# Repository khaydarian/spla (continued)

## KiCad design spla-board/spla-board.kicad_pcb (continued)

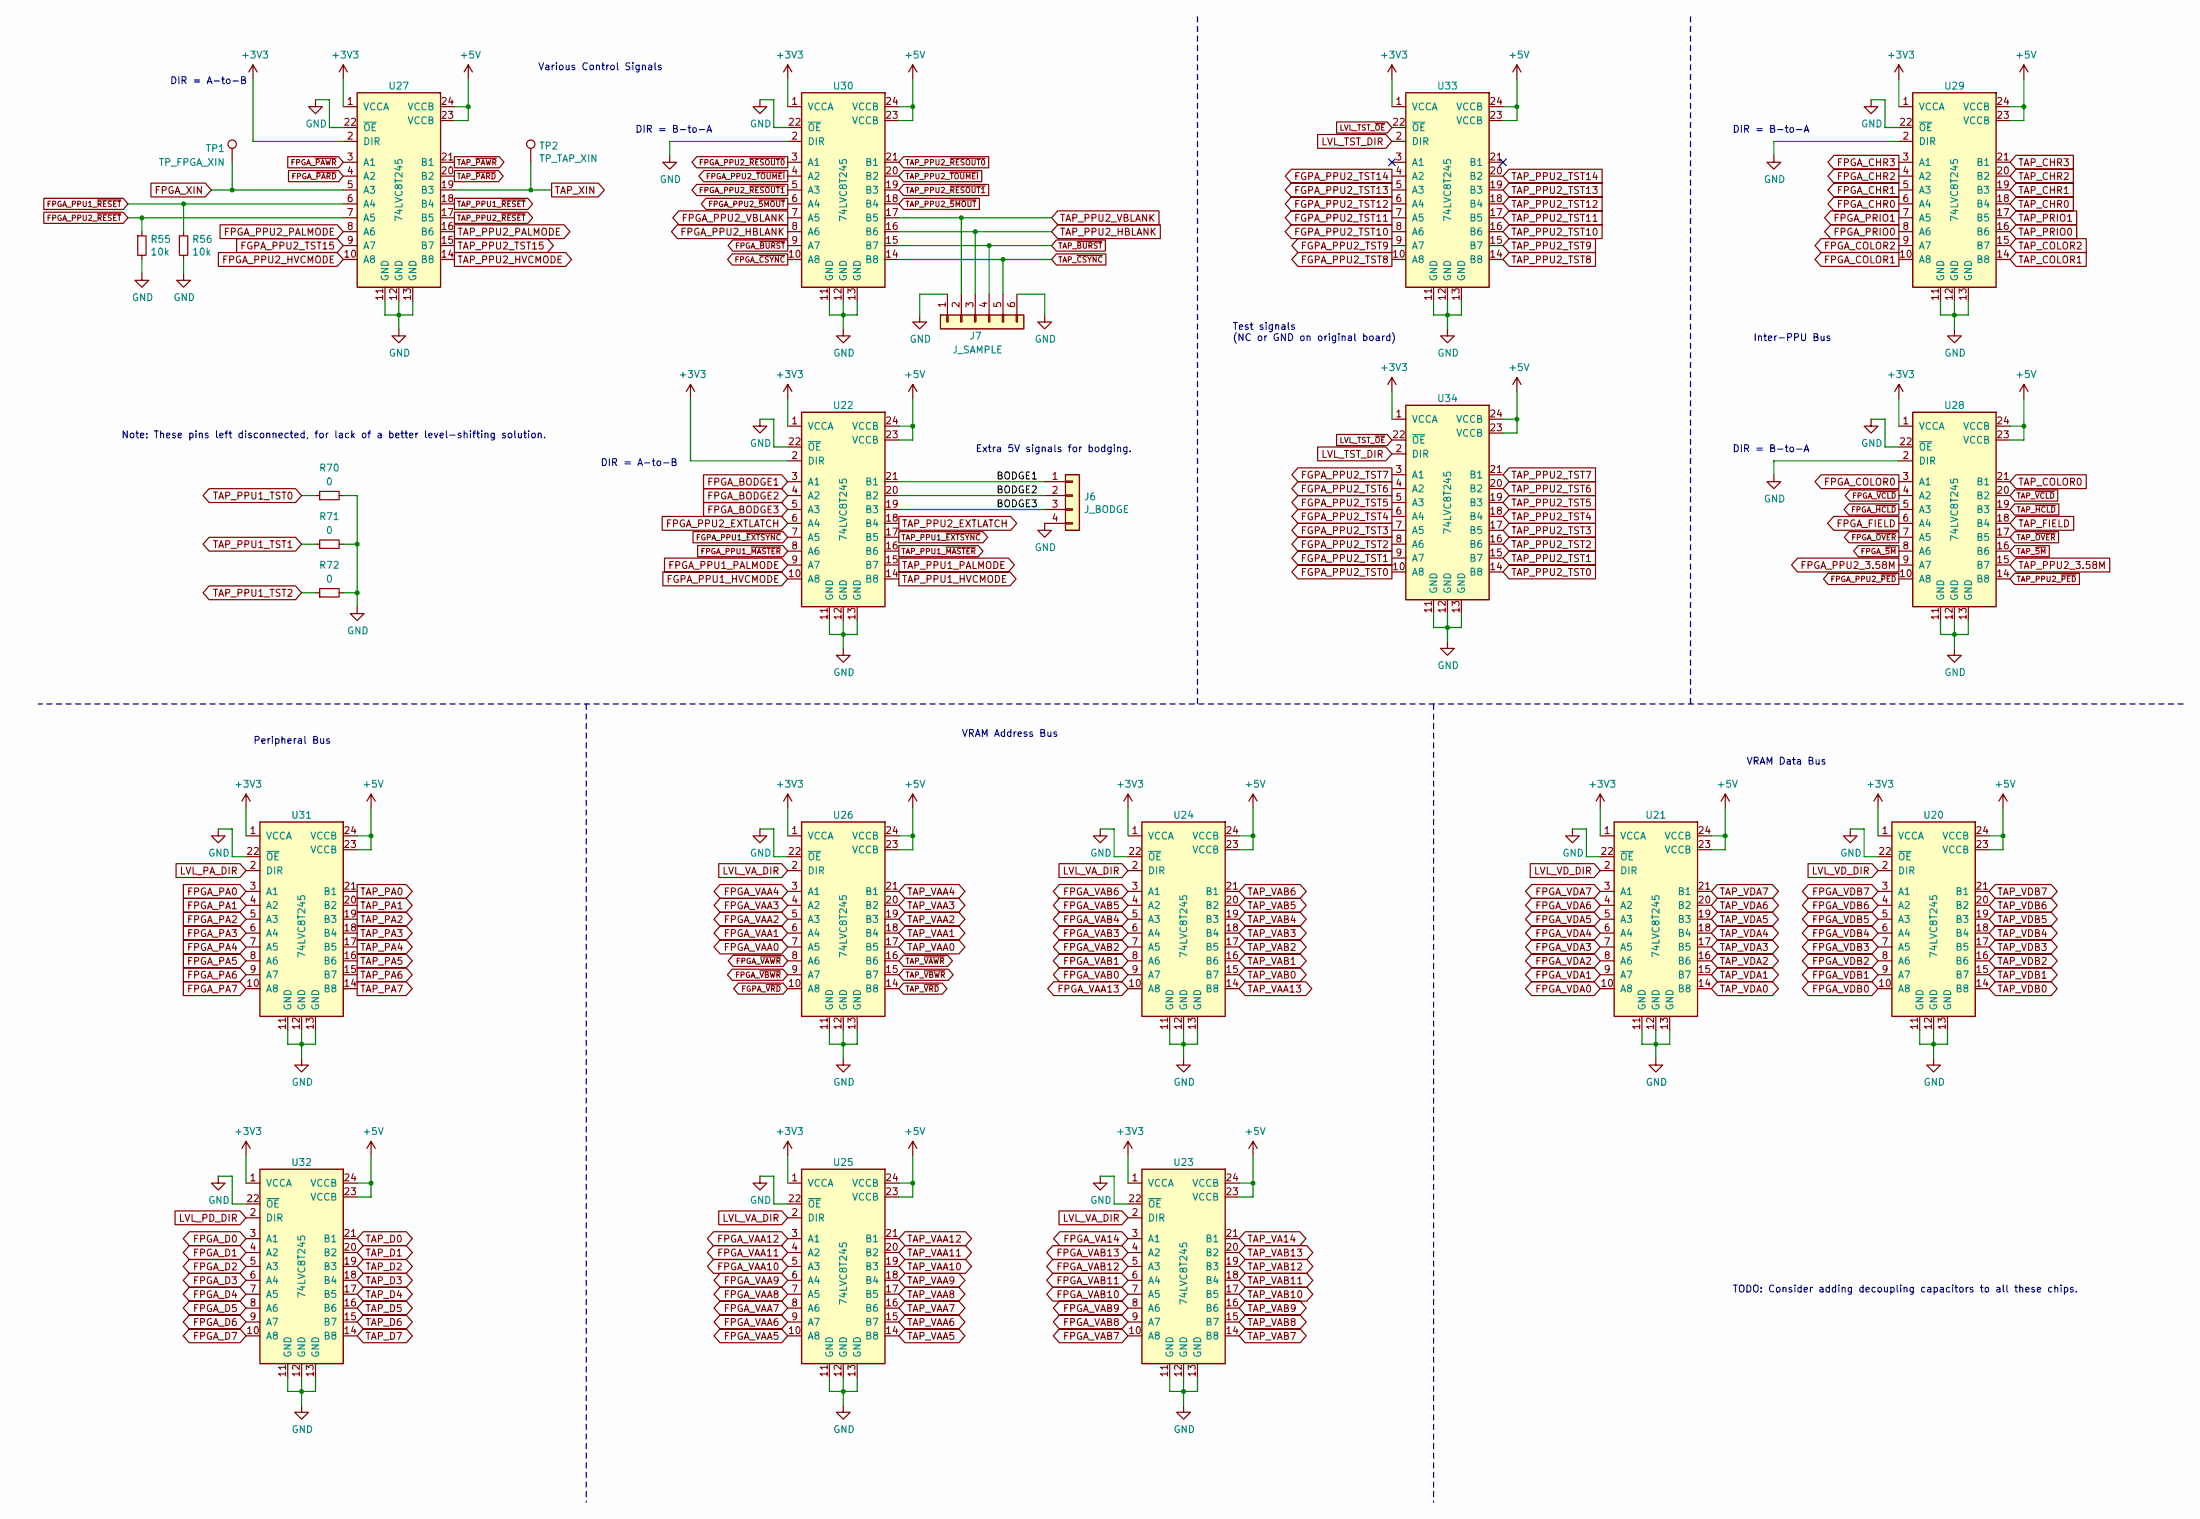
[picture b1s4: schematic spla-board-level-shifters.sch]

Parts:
J6: J_BODGE; PinHeader_1x04_P2.54mm_Vertical; Digikey S1011EC-40-ND
J7: J_SAMPLE; PinHeader_1x06_P2.54mm_Vertical; Digikey S1011EC-40-ND
R55, R56: 10k; R_0603_1608Metric; Digikey RMCF0603JT10K0CT-ND
R70, R71, R72: 0; R_0603_1608Metric; Digikey 2019-RK73Z1JTTDCT-ND
TP1: TP_FPGA_XIN; TestPoint_Pad_D1.0mm; Digikey N/A
TP2: TP_TAP_XIN; TestPoint_Pad_D1.0mm; Digikey N/A
U20, U21, U22, U23, U24, U25, U26, U27, U28, U29, U30, U31, U32, U33, U34: 74LVC8T245; TSSOP-24_4.4x7.8mm_P0.65mm; Digikey 296-18593-1-ND

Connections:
+5V: U20.23 (VCCB), U20.24 (VCCB), U21.23 (VCCB), U21.24 (VCCB), U22.23 (VCCB), U22.24 (VCCB), U23.23 (VCCB), U23.24 (VCCB), U24.23 (VCCB), U24.24 (VCCB), U25.23 (VCCB), U25.24 (VCCB), U26.23 (VCCB), U26.24 (VCCB), U27.23 (VCCB), U27.24 (VCCB), U28.23 (VCCB), U28.24 (VCCB), U29.23 (VCCB), U29.24 (VCCB), U30.23 (VCCB), U30.24 (VCCB), U31.23 (VCCB), U31.24 (VCCB), U32.23 (VCCB), U32.24 (VCCB), U33.23 (VCCB), U33.24 (VCCB), U34.23 (VCCB), U34.24 (VCCB); also elsewhere on the board
/SPLA Board - Level Shifters/BODGE1: J6.1, U22.21 (B1)
/SPLA Board - Level Shifters/BODGE2: J6.2, U22.20 (B2)
/SPLA Board - Level Shifters/BODGE3: J6.3, U22.19 (B3)
FGPA_PPU1_HVCMODE: U22.10 (A8); also elsewhere on the board
FGPA_PPU1_~EXTSYNC~: U22.7 (A5); also elsewhere on the board
FGPA_PPU2_TST0: U34.10 (A8); also elsewhere on the board
FGPA_PPU2_TST1: U34.9 (A7); also elsewhere on the board
FGPA_PPU2_TST2: U34.8 (A6); also elsewhere on the board
FGPA_PPU2_TST3: U34.7 (A5); also elsewhere on the board
FGPA_PPU2_TST4: U34.6 (A4); also elsewhere on the board
FGPA_PPU2_TST5: U34.5 (A3); also elsewhere on the board
FGPA_PPU2_TST6: U34.4 (A2); also elsewhere on the board
FGPA_PPU2_TST7: U34.3 (A1); also elsewhere on the board
FGPA_PPU2_TST8: U33.10 (A8); also elsewhere on the board
FGPA_PPU2_TST9: U33.9 (A7); also elsewhere on the board
FGPA_PPU2_TST10: U33.8 (A6); also elsewhere on the board
FGPA_PPU2_TST11: U33.7 (A5); also elsewhere on the board
FGPA_PPU2_TST12: U33.6 (A4); also elsewhere on the board
FGPA_PPU2_TST13: U33.5 (A3); also elsewhere on the board
FGPA_PPU2_TST14: U33.4 (A2); also elsewhere on the board
FGPA_PPU2_TST15: U27.9 (A7); also elsewhere on the board
FGPA_~VRD~: U26.10 (A8); also elsewhere on the board
FPGA_BODGE1: U22.3 (A1); also elsewhere on the board
FPGA_BODGE2: U22.4 (A2); also elsewhere on the board
FPGA_BODGE3: U22.5 (A3); also elsewhere on the board
FPGA_CHR0: U29.6 (A4); also elsewhere on the board
FPGA_CHR1: U29.5 (A3); also elsewhere on the board
FPGA_CHR2: U29.4 (A2); also elsewhere on the board
FPGA_CHR3: U29.3 (A1); also elsewhere on the board
FPGA_COLOR0: U28.3 (A1); also elsewhere on the board
FPGA_COLOR1: U29.10 (A8); also elsewhere on the board
FPGA_COLOR2: U29.9 (A7); also elsewhere on the board
FPGA_D0: U32.3 (A1); also elsewhere on the board
FPGA_D1: U32.4 (A2); also elsewhere on the board
FPGA_D2: U32.5 (A3); also elsewhere on the board
FPGA_D3: U32.6 (A4); also elsewhere on the board
FPGA_D4: U32.7 (A5); also elsewhere on the board
FPGA_D5: U32.8 (A6); also elsewhere on the board
FPGA_D6: U32.9 (A7); also elsewhere on the board
FPGA_D7: U32.10 (A8); also elsewhere on the board
FPGA_FIELD: U28.6 (A4); also elsewhere on the board
FPGA_PA0: U31.3 (A1); also elsewhere on the board
FPGA_PA1: U31.4 (A2); also elsewhere on the board
FPGA_PA2: U31.5 (A3); also elsewhere on the board
FPGA_PA3: U31.6 (A4); also elsewhere on the board
FPGA_PA4: U31.7 (A5); also elsewhere on the board
FPGA_PA5: U31.8 (A6); also elsewhere on the board
FPGA_PA6: U31.9 (A7); also elsewhere on the board
FPGA_PA7: U31.10 (A8); also elsewhere on the board
FPGA_PPU1_PALMODE: U22.9 (A7); also elsewhere on the board
FPGA_PPU1_~MASTER~: U22.8 (A6); also elsewhere on the board
FPGA_PPU1_~RESET~: R56.1, U27.6 (A4); also elsewhere on the board
FPGA_PPU2_3.58M: U28.9 (A7); also elsewhere on the board
FPGA_PPU2_EXTLATCH: U22.6 (A4); also elsewhere on the board
FPGA_PPU2_HBLANK: U30.8 (A6); also elsewhere on the board
FPGA_PPU2_HVCMODE: U27.10 (A8); also elsewhere on the board
FPGA_PPU2_PALMODE: U27.8 (A6); also elsewhere on the board
FPGA_PPU2_VBLANK: U30.7 (A5); also elsewhere on the board
FPGA_PPU2_~5MOUT~: U30.6 (A4); also elsewhere on the board
FPGA_PPU2_~PED~: U28.10 (A8); also elsewhere on the board
FPGA_PPU2_~RESET~: R55.1, U27.7 (A5); also elsewhere on the board
FPGA_PPU2_~RESOUT0~: U30.3 (A1); also elsewhere on the board
FPGA_PPU2_~RESOUT1~: U30.5 (A3); also elsewhere on the board
FPGA_PPU2_~TOUMEI~: U30.4 (A2); also elsewhere on the board
FPGA_PRIO0: U29.8 (A6); also elsewhere on the board
FPGA_PRIO1: U29.7 (A5); also elsewhere on the board
FPGA_VA14: U23.3 (A1); also elsewhere on the board
FPGA_VAA0: U26.7 (A5); also elsewhere on the board
FPGA_VAA1: U26.6 (A4); also elsewhere on the board
FPGA_VAA2: U26.5 (A3); also elsewhere on the board
FPGA_VAA3: U26.4 (A2); also elsewhere on the board
FPGA_VAA4: U26.3 (A1); also elsewhere on the board
FPGA_VAA5: U25.10 (A8); also elsewhere on the board
FPGA_VAA6: U25.9 (A7); also elsewhere on the board
FPGA_VAA7: U25.8 (A6); also elsewhere on the board
FPGA_VAA8: U25.7 (A5); also elsewhere on the board
FPGA_VAA9: U25.6 (A4); also elsewhere on the board
FPGA_VAA10: U25.5 (A3); also elsewhere on the board
FPGA_VAA11: U25.4 (A2); also elsewhere on the board
FPGA_VAA12: U25.3 (A1); also elsewhere on the board
FPGA_VAA13: U24.10 (A8); also elsewhere on the board
FPGA_VAB0: U24.9 (A7); also elsewhere on the board
FPGA_VAB1: U24.8 (A6); also elsewhere on the board
FPGA_VAB2: U24.7 (A5); also elsewhere on the board
FPGA_VAB3: U24.6 (A4); also elsewhere on the board
FPGA_VAB4: U24.5 (A3); also elsewhere on the board
FPGA_VAB5: U24.4 (A2); also elsewhere on the board
FPGA_VAB6: U24.3 (A1); also elsewhere on the board
FPGA_VAB7: U23.10 (A8); also elsewhere on the board
FPGA_VAB8: U23.9 (A7); also elsewhere on the board
FPGA_VAB9: U23.8 (A6); also elsewhere on the board
FPGA_VAB10: U23.7 (A5); also elsewhere on the board
FPGA_VAB11: U23.6 (A4); also elsewhere on the board
FPGA_VAB12: U23.5 (A3); also elsewhere on the board
FPGA_VAB13: U23.4 (A2); also elsewhere on the board
FPGA_VDA0: U21.10 (A8); also elsewhere on the board
FPGA_VDA1: U21.9 (A7); also elsewhere on the board
FPGA_VDA2: U21.8 (A6); also elsewhere on the board
FPGA_VDA3: U21.7 (A5); also elsewhere on the board
FPGA_VDA4: U21.6 (A4); also elsewhere on the board
FPGA_VDA5: U21.5 (A3); also elsewhere on the board
FPGA_VDA6: U21.4 (A2); also elsewhere on the board
FPGA_VDA7: U21.3 (A1); also elsewhere on the board
FPGA_VDB0: U20.10 (A8); also elsewhere on the board
FPGA_VDB1: U20.9 (A7); also elsewhere on the board
FPGA_VDB2: U20.8 (A6); also elsewhere on the board
FPGA_VDB3: U20.7 (A5); also elsewhere on the board
FPGA_VDB4: U20.6 (A4); also elsewhere on the board
FPGA_VDB5: U20.5 (A3); also elsewhere on the board
FPGA_VDB6: U20.4 (A2); also elsewhere on the board
FPGA_VDB7: U20.3 (A1); also elsewhere on the board
FPGA_XIN: TP1.1, U27.5 (A3); also elsewhere on the board
FPGA_~5M~: U28.8 (A6); also elsewhere on the board
FPGA_~BURST~: U30.9 (A7); also elsewhere on the board
FPGA_~CSYNC~: U30.10 (A8); also elsewhere on the board
FPGA_~HCLD: U28.5 (A3); also elsewhere on the board
FPGA_~OVER~: U28.7 (A5); also elsewhere on the board
FPGA_~PARD~: U27.4 (A2); also elsewhere on the board
FPGA_~PAWR~: U27.3 (A1); also elsewhere on the board
FPGA_~VAWR~: U26.8 (A6); also elsewhere on the board
FPGA_~VBWR~: U26.9 (A7); also elsewhere on the board
FPGA_~VCLD~: U28.4 (A2); also elsewhere on the board
GND: J6.4, J7.1, J7.6, R55.2, R56.2, R70.2, R71.2, R72.2, U20.11 (GND), U20.12 (GND), U20.13 (GND), U20.22 (~OE), U21.11 (GND), U21.12 (GND), U21.13 (GND), U21.22 (~OE), U22.11 (GND), U22.12 (GND), U22.13 (GND), U22.22 (~OE), U23.11 (GND), U23.12 (GND), U23.13 (GND), U23.22 (~OE), U24.11 (GND), U24.12 (GND), U24.13 (GND), U24.22 (~OE), U25.11 (GND), U25.12 (GND), U25.13 (GND), U25.22 (~OE), U26.11 (GND), U26.12 (GND), U26.13 (GND), U26.22 (~OE), U27.11 (GND), U27.12 (GND), U27.13 (GND), U27.22 (~OE), U28.2 (DIR), U28.11 (GND), U28.12 (GND), U28.13 (GND), U28.22 (~OE), U29.2 (DIR), U29.11 (GND), U29.12 (GND), U29.13 (GND), U29.22 (~OE), U30.2 (DIR), U30.11 (GND), U30.12 (GND), U30.13 (GND), U30.22 (~OE), U31.11 (GND), U31.12 (GND), U31.13 (GND), U31.22 (~OE), U32.11 (GND), U32.12 (GND), U32.13 (GND), U32.22 (~OE), U33.11 (GND), U33.12 (GND), U33.13 (GND), U34.11 (GND), U34.12 (GND), U34.13 (GND); also elsewhere on the board
LVL_PA_DIR: U31.2 (DIR); also elsewhere on the board
LVL_PD_DIR: U32.2 (DIR); also elsewhere on the board
LVL_TST_DIR: U33.2 (DIR), U34.2 (DIR); also elsewhere on the board
LVL_TST_~OE~: U33.22 (~OE), U34.22 (~OE); also elsewhere on the board
LVL_VA_DIR: U23.2 (DIR), U24.2 (DIR), U25.2 (DIR), U26.2 (DIR); also elsewhere on the board
LVL_VD_DIR: U20.2 (DIR), U21.2 (DIR); also elsewhere on the board
TAP_CHR0: U29.18 (B4); also elsewhere on the board
TAP_CHR1: U29.19 (B3); also elsewhere on the board
TAP_CHR2: U29.20 (B2); also elsewhere on the board
TAP_CHR3: U29.21 (B1); also elsewhere on the board
TAP_COLOR0: U28.21 (B1); also elsewhere on the board
TAP_COLOR1: U29.14 (B8); also elsewhere on the board
TAP_COLOR2: U29.15 (B7); also elsewhere on the board
TAP_D0: U32.21 (B1); also elsewhere on the board
TAP_D1: U32.20 (B2); also elsewhere on the board
TAP_D2: U32.19 (B3); also elsewhere on the board
TAP_D3: U32.18 (B4); also elsewhere on the board
TAP_D4: U32.17 (B5); also elsewhere on the board
TAP_D5: U32.16 (B6); also elsewhere on the board
TAP_D6: U32.15 (B7); also elsewhere on the board
TAP_D7: U32.14 (B8); also elsewhere on the board
TAP_FIELD: U28.18 (B4); also elsewhere on the board
TAP_PA0: U31.21 (B1); also elsewhere on the board
TAP_PA1: U31.20 (B2); also elsewhere on the board
TAP_PA2: U31.19 (B3); also elsewhere on the board
TAP_PA3: U31.18 (B4); also elsewhere on the board
TAP_PA4: U31.17 (B5); also elsewhere on the board
TAP_PA5: U31.16 (B6); also elsewhere on the board
TAP_PA6: U31.15 (B7); also elsewhere on the board
TAP_PA7: U31.14 (B8); also elsewhere on the board
TAP_PPU1_HVCMODE: U22.14 (B8); also elsewhere on the board
TAP_PPU1_PALMODE: U22.15 (B7); also elsewhere on the board
TAP_PPU1_TST0: R70.1; also elsewhere on the board
TAP_PPU1_TST1: R71.1; also elsewhere on the board
TAP_PPU1_TST2: R72.1; also elsewhere on the board
TAP_PPU1_~EXTSYNC~: U22.17 (B5); also elsewhere on the board
TAP_PPU1_~MASTER~: U22.16 (B6); also elsewhere on the board
TAP_PPU1_~RESET~: U27.18 (B4); also elsewhere on the board
TAP_PPU2_3.58M: U28.15 (B7); also elsewhere on the board
TAP_PPU2_EXTLATCH: U22.18 (B4); also elsewhere on the board
TAP_PPU2_HBLANK: J7.3, U30.16 (B6); also elsewhere on the board
TAP_PPU2_HVCMODE: U27.14 (B8); also elsewhere on the board
TAP_PPU2_PALMODE: U27.16 (B6); also elsewhere on the board
TAP_PPU2_TST0: U34.14 (B8); also elsewhere on the board
TAP_PPU2_TST1: U34.15 (B7); also elsewhere on the board
TAP_PPU2_TST2: U34.16 (B6); also elsewhere on the board
TAP_PPU2_TST3: U34.17 (B5); also elsewhere on the board
TAP_PPU2_TST4: U34.18 (B4); also elsewhere on the board
TAP_PPU2_TST5: U34.19 (B3); also elsewhere on the board
TAP_PPU2_TST6: U34.20 (B2); also elsewhere on the board
TAP_PPU2_TST7: U34.21 (B1); also elsewhere on the board
TAP_PPU2_TST8: U33.14 (B8); also elsewhere on the board
TAP_PPU2_TST9: U33.15 (B7); also elsewhere on the board
TAP_PPU2_TST10: U33.16 (B6); also elsewhere on the board
TAP_PPU2_TST11: U33.17 (B5); also elsewhere on the board
TAP_PPU2_TST12: U33.18 (B4); also elsewhere on the board
TAP_PPU2_TST13: U33.19 (B3); also elsewhere on the board
TAP_PPU2_TST14: U33.20 (B2); also elsewhere on the board
TAP_PPU2_TST15: U27.15 (B7); also elsewhere on the board
TAP_PPU2_VBLANK: J7.2, U30.17 (B5); also elsewhere on the board
TAP_PPU2_~5MOUT~: U30.18 (B4); also elsewhere on the board
TAP_PPU2_~PED~: U28.14 (B8); also elsewhere on the board
TAP_PPU2_~RESET~: U27.17 (B5); also elsewhere on the board
TAP_PPU2_~RESOUT0~: U30.21 (B1); also elsewhere on the board
TAP_PPU2_~RESOUT1~: U30.19 (B3); also elsewhere on the board
TAP_PPU2_~TOUMEI~: U30.20 (B2); also elsewhere on the board
TAP_PRIO0: U29.16 (B6); also elsewhere on the board
TAP_PRIO1: U29.17 (B5); also elsewhere on the board
TAP_VA14: U23.21 (B1); also elsewhere on the board
TAP_VAA0: U26.17 (B5); also elsewhere on the board
TAP_VAA1: U26.18 (B4); also elsewhere on the board
TAP_VAA2: U26.19 (B3); also elsewhere on the board
TAP_VAA3: U26.20 (B2); also elsewhere on the board
TAP_VAA4: U26.21 (B1); also elsewhere on the board
TAP_VAA5: U25.14 (B8); also elsewhere on the board
TAP_VAA6: U25.15 (B7); also elsewhere on the board
TAP_VAA7: U25.16 (B6); also elsewhere on the board
TAP_VAA8: U25.17 (B5); also elsewhere on the board
TAP_VAA9: U25.18 (B4); also elsewhere on the board
TAP_VAA10: U25.19 (B3); also elsewhere on the board
TAP_VAA11: U25.20 (B2); also elsewhere on the board
TAP_VAA12: U25.21 (B1); also elsewhere on the board
TAP_VAA13: U24.14 (B8); also elsewhere on the board
TAP_VAB0: U24.15 (B7); also elsewhere on the board
TAP_VAB1: U24.16 (B6); also elsewhere on the board
TAP_VAB2: U24.17 (B5); also elsewhere on the board
TAP_VAB3: U24.18 (B4); also elsewhere on the board
TAP_VAB4: U24.19 (B3); also elsewhere on the board
TAP_VAB5: U24.20 (B2); also elsewhere on the board
TAP_VAB6: U24.21 (B1); also elsewhere on the board
TAP_VAB7: U23.14 (B8); also elsewhere on the board
TAP_VAB8: U23.15 (B7); also elsewhere on the board
TAP_VAB9: U23.16 (B6); also elsewhere on the board
TAP_VAB10: U23.17 (B5); also elsewhere on the board
TAP_VAB11: U23.18 (B4); also elsewhere on the board
TAP_VAB12: U23.19 (B3); also elsewhere on the board
TAP_VAB13: U23.20 (B2); also elsewhere on the board
TAP_VDA0: U21.14 (B8); also elsewhere on the board
TAP_VDA1: U21.15 (B7); also elsewhere on the board
TAP_VDA2: U21.16 (B6); also elsewhere on the board
TAP_VDA3: U21.17 (B5); also elsewhere on the board
TAP_VDA4: U21.18 (B4); also elsewhere on the board
TAP_VDA5: U21.19 (B3); also elsewhere on the board
TAP_VDA6: U21.20 (B2); also elsewhere on the board
TAP_VDA7: U21.21 (B1); also elsewhere on the board
TAP_VDB0: U20.14 (B8); also elsewhere on the board
TAP_VDB1: U20.15 (B7); also elsewhere on the board
TAP_VDB2: U20.16 (B6); also elsewhere on the board
TAP_VDB3: U20.17 (B5); also elsewhere on the board
TAP_VDB4: U20.18 (B4); also elsewhere on the board
TAP_VDB5: U20.19 (B3); also elsewhere on the board
TAP_VDB6: U20.20 (B2); also elsewhere on the board
TAP_VDB7: U20.21 (B1); also elsewhere on the board
TAP_XIN: TP2.1, U27.19 (B3); also elsewhere on the board
TAP_~5M~: U28.16 (B6); also elsewhere on the board
TAP_~BURST~: J7.4, U30.15 (B7); also elsewhere on the board
TAP_~CSYNC~: J7.5, U30.14 (B8); also elsewhere on the board
TAP_~HCLD~: U28.19 (B3); also elsewhere on the board
TAP_~OVER~: U28.17 (B5); also elsewhere on the board
TAP_~PARD~: U27.20 (B2); also elsewhere on the board
TAP_~PAWR~: U27.21 (B1); also elsewhere on the board
TAP_~VAWR~: U26.16 (B6); also elsewhere on the board
TAP_~VBWR~: U26.15 (B7); also elsewhere on the board
TAP_~VCLD~: U28.20 (B2); also elsewhere on the board
TAP_~VRD~: U26.14 (B8); also elsewhere on the board

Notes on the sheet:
Peripheral Bus
VRAM Address Bus
VRAM Data Bus
Inter-PPU Bus
Extra 5V signals for bodging.
TODO: Consider adding decoupling capacitors to all these chips.
Test signals (NC or GND on original board)
Note: These pins left disconnected, for lack of a better level-shifting solution.
Various Control Signals
DIR = B-to-A
DIR = A-to-B

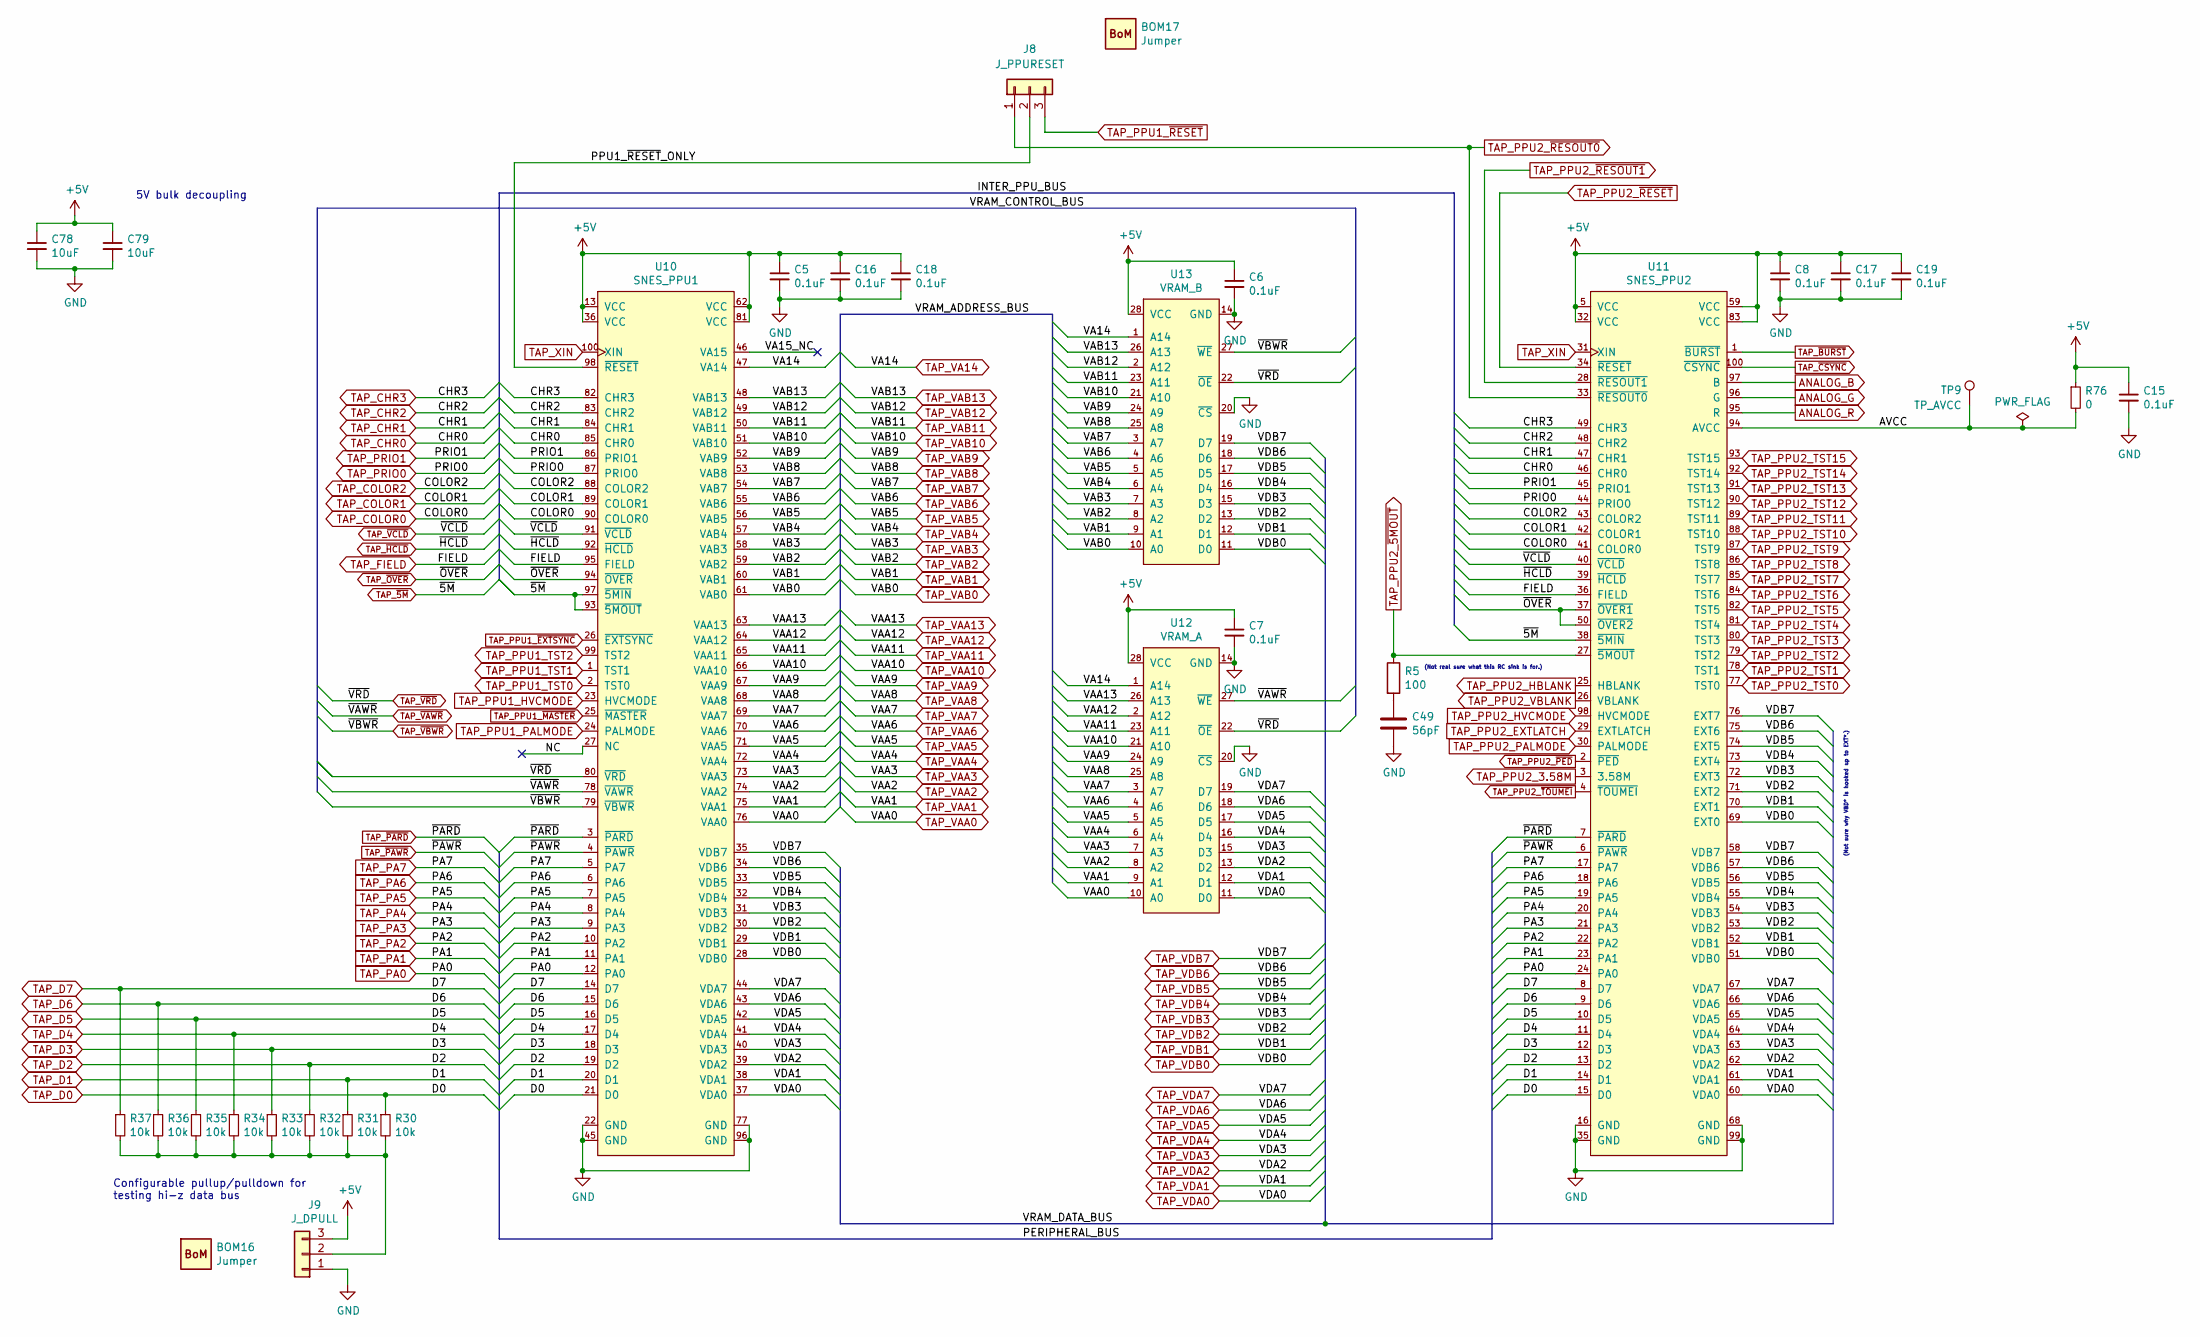
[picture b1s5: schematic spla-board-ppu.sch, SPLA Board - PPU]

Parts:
BOM16, BOM17: Jumper; BoM; Digikey S9337-ND
C5, C6, C7, C8, C15, C16, C17, C18, C19: 0.1uF; C_0603_1608Metric; Digikey 490-16477-1-ND
C49: 56pF; C_0603_1608Metric; Digikey 490-17769-1-ND
C78, C79: 10uF; C_0805_2012Metric; Digikey 490-10516-1-ND
J8: J_PPURESET; PinHeader_1x03_P2.54mm_Vertical; Digikey S1011EC-40-ND
J9: J_DPULL; PinHeader_1x03_P2.54mm_Vertical; Digikey S1011EC-40-ND
R5: 100; R_0603_1608Metric; Digikey RMCF0603JT100RCT-ND
R30, R31, R32, R33, R34, R35, R36, R37: 10k; R_0603_1608Metric; Digikey RMCF0603JT10K0CT-ND
R76: 0; R_0603_1608Metric; Digikey 2019-RK73Z1JTTDCT-ND
TP9: TP_AVCC; TestPoint_Pad_D1.0mm; Digikey N/A
U10: SNES_PPU1; QFP-100_14x20mm_P0.65mm; Digikey N/A
U11: SNES_PPU2; QFP-100_14x20mm_P0.65mm; Digikey N/A
U12: VRAM_A; SOP-28_17x8mm_P1.27mm; Digikey N/A
U13: VRAM_B; SOP-28_17x8mm_P1.27mm; Digikey N/A

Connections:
+5V: C5.1, C6.1, C7.1, C8.1, C15.1, C16.1, C17.1, C18.1, C19.1, C78.1, C79.1, J9.3, R76.1, U10.13 (VCC), U10.36 (VCC), U10.62 (VCC), U10.81 (VCC), U11.5 (VCC), U11.32 (VCC), U11.59 (VCC), U11.83 (VCC), U12.28 (VCC), U13.28 (VCC); also elsewhere on the board
/SPLA Board - PPU/AVCC: R76.2, TP9.1, U11.94 (AVCC)
/SPLA Board - PPU/NC: U10.27 (NC)
/SPLA Board - PPU/PPU1_~RESET~_ONLY: J8.2, U10.98 (~RESET)
/SPLA Board - PPU/VA15_NC: U10.46 (VA15)
ANALOG_B: U11.97 (B); also elsewhere on the board
ANALOG_G: U11.96 (G); also elsewhere on the board
ANALOG_R: U11.95 (R); also elsewhere on the board
GND: C5.2, C6.2, C7.2, C8.2, C15.2, C16.2, C17.2, C18.2, C19.2, C49.2, C78.2, C79.2, J9.1, U10.22 (GND), U10.45 (GND), U10.77 (GND), U10.96 (GND), U11.16 (GND), U11.35 (GND), U11.68 (GND), U11.99 (GND), U12.14 (GND), U12.20 (~CS), U13.14 (GND), U13.20 (~CS); also elsewhere on the board
unnamed: C49.1, R5.2
unnamed: J9.2, R30.2, R31.2, R32.2, R33.2, R34.2, R35.2, R36.2, R37.2
TAP_CHR0: U10.85 (CHR0), U11.46 (CHR0); also elsewhere on the board
TAP_CHR1: U10.84 (CHR1), U11.47 (CHR1); also elsewhere on the board
TAP_CHR2: U10.83 (CHR2), U11.48 (CHR2); also elsewhere on the board
TAP_CHR3: U10.82 (CHR3), U11.49 (CHR3); also elsewhere on the board
TAP_COLOR0: U10.90 (COLOR0), U11.41 (COLOR0); also elsewhere on the board
TAP_COLOR1: U10.89 (COLOR1), U11.42 (COLOR1); also elsewhere on the board
TAP_COLOR2: U10.88 (COLOR2), U11.43 (COLOR2); also elsewhere on the board
TAP_D0: R30.1, U10.21 (D0), U11.15 (D0); also elsewhere on the board
TAP_D1: R31.1, U10.20 (D1), U11.14 (D1); also elsewhere on the board
TAP_D2: R32.1, U10.19 (D2), U11.13 (D2); also elsewhere on the board
TAP_D3: R33.1, U10.18 (D3), U11.12 (D3); also elsewhere on the board
TAP_D4: R34.1, U10.17 (D4), U11.11 (D4); also elsewhere on the board
TAP_D5: R35.1, U10.16 (D5), U11.10 (D5); also elsewhere on the board
TAP_D6: R36.1, U10.15 (D6), U11.9 (D6); also elsewhere on the board
TAP_D7: R37.1, U10.14 (D7), U11.8 (D7); also elsewhere on the board
TAP_FIELD: U10.95 (FIELD), U11.36 (FIELD); also elsewhere on the board
TAP_PA0: U10.12 (PA0), U11.24 (PA0); also elsewhere on the board
TAP_PA1: U10.11 (PA1), U11.23 (PA1); also elsewhere on the board
TAP_PA2: U10.10 (PA2), U11.22 (PA2); also elsewhere on the board
TAP_PA3: U10.9 (PA3), U11.21 (PA3); also elsewhere on the board
TAP_PA4: U10.8 (PA4), U11.20 (PA4); also elsewhere on the board
TAP_PA5: U10.7 (PA5), U11.19 (PA5); also elsewhere on the board
TAP_PA6: U10.6 (PA6), U11.18 (PA6); also elsewhere on the board
TAP_PA7: U10.5 (PA7), U11.17 (PA7); also elsewhere on the board
TAP_PPU1_HVCMODE: U10.23 (HVCMODE); also elsewhere on the board
TAP_PPU1_PALMODE: U10.24 (PALMODE); also elsewhere on the board
TAP_PPU1_TST0: U10.2 (TST0); also elsewhere on the board
TAP_PPU1_TST1: U10.1 (TST1); also elsewhere on the board
TAP_PPU1_TST2: U10.99 (TST2); also elsewhere on the board
TAP_PPU1_~EXTSYNC~: U10.26 (~EXTSYNC); also elsewhere on the board
TAP_PPU1_~MASTER~: U10.25 (~MASTER); also elsewhere on the board
TAP_PPU1_~RESET~: J8.3; also elsewhere on the board
TAP_PPU2_3.58M: U11.3 (3.58M); also elsewhere on the board
TAP_PPU2_EXTLATCH: U11.29 (EXTLATCH); also elsewhere on the board
TAP_PPU2_HBLANK: U11.25 (HBLANK); also elsewhere on the board
TAP_PPU2_HVCMODE: U11.98 (HVCMODE); also elsewhere on the board
TAP_PPU2_PALMODE: U11.30 (PALMODE); also elsewhere on the board
TAP_PPU2_TST0: U11.77 (TST0); also elsewhere on the board
TAP_PPU2_TST1: U11.78 (TST1); also elsewhere on the board
TAP_PPU2_TST2: U11.79 (TST2); also elsewhere on the board
TAP_PPU2_TST3: U11.80 (TST3); also elsewhere on the board
TAP_PPU2_TST4: U11.81 (TST4); also elsewhere on the board
TAP_PPU2_TST5: U11.82 (TST5); also elsewhere on the board
TAP_PPU2_TST6: U11.84 (TST6); also elsewhere on the board
TAP_PPU2_TST7: U11.85 (TST7); also elsewhere on the board
TAP_PPU2_TST8: U11.86 (TST8); also elsewhere on the board
TAP_PPU2_TST9: U11.87 (TST9); also elsewhere on the board
TAP_PPU2_TST10: U11.88 (TST10); also elsewhere on the board
TAP_PPU2_TST11: U11.89 (TST11); also elsewhere on the board
TAP_PPU2_TST12: U11.90 (TST12); also elsewhere on the board
TAP_PPU2_TST13: U11.91 (TST13); also elsewhere on the board
TAP_PPU2_TST14: U11.92 (TST14); also elsewhere on the board
TAP_PPU2_TST15: U11.93 (TST15); also elsewhere on the board
TAP_PPU2_VBLANK: U11.26 (VBLANK); also elsewhere on the board
TAP_PPU2_~5MOUT~: R5.1, U11.27 (~5MOUT); also elsewhere on the board
TAP_PPU2_~PED~: U11.2 (~PED); also elsewhere on the board
TAP_PPU2_~RESET~: U11.34 (~RESET); also elsewhere on the board
TAP_PPU2_~RESOUT0~: J8.1, U11.33 (~RESOUT0); also elsewhere on the board
TAP_PPU2_~RESOUT1~: U11.28 (~RESOUT1); also elsewhere on the board
TAP_PPU2_~TOUMEI~: U11.4 (~TOUMEI); also elsewhere on the board
TAP_PRIO0: U10.87 (PRIO0), U11.44 (PRIO0); also elsewhere on the board
TAP_PRIO1: U10.86 (PRIO1), U11.45 (PRIO1); also elsewhere on the board
TAP_VA14: U10.47 (VA14), U12.1 (A14), U13.1 (A14); also elsewhere on the board
TAP_VAA0: U10.76 (VAA0), U12.10 (A0); also elsewhere on the board
TAP_VAA1: U10.75 (VAA1), U12.9 (A1); also elsewhere on the board
TAP_VAA2: U10.74 (VAA2), U12.8 (A2); also elsewhere on the board
TAP_VAA3: U10.73 (VAA3), U12.7 (A3); also elsewhere on the board
TAP_VAA4: U10.72 (VAA4), U12.6 (A4); also elsewhere on the board
TAP_VAA5: U10.71 (VAA5), U12.5 (A5); also elsewhere on the board
TAP_VAA6: U10.70 (VAA6), U12.4 (A6); also elsewhere on the board
TAP_VAA7: U10.69 (VAA7), U12.3 (A7); also elsewhere on the board
TAP_VAA8: U10.68 (VAA8), U12.25 (A8); also elsewhere on the board
TAP_VAA9: U10.67 (VAA9), U12.24 (A9); also elsewhere on the board
TAP_VAA10: U10.66 (VAA10), U12.21 (A10); also elsewhere on the board
TAP_VAA11: U10.65 (VAA11), U12.23 (A11); also elsewhere on the board
TAP_VAA12: U10.64 (VAA12), U12.2 (A12); also elsewhere on the board
TAP_VAA13: U10.63 (VAA13), U12.26 (A13); also elsewhere on the board
TAP_VAB0: U10.61 (VAB0), U13.10 (A0); also elsewhere on the board
TAP_VAB1: U10.60 (VAB1), U13.9 (A1); also elsewhere on the board
TAP_VAB2: U10.59 (VAB2), U13.8 (A2); also elsewhere on the board
TAP_VAB3: U10.58 (VAB3), U13.7 (A3); also elsewhere on the board
TAP_VAB4: U10.57 (VAB4), U13.6 (A4); also elsewhere on the board
TAP_VAB5: U10.56 (VAB5), U13.5 (A5); also elsewhere on the board
TAP_VAB6: U10.55 (VAB6), U13.4 (A6); also elsewhere on the board
TAP_VAB7: U10.54 (VAB7), U13.3 (A7); also elsewhere on the board
TAP_VAB8: U10.53 (VAB8), U13.25 (A8); also elsewhere on the board
TAP_VAB9: U10.52 (VAB9), U13.24 (A9); also elsewhere on the board
TAP_VAB10: U10.51 (VAB10), U13.21 (A10); also elsewhere on the board
TAP_VAB11: U10.50 (VAB11), U13.23 (A11); also elsewhere on the board
TAP_VAB12: U10.49 (VAB12), U13.2 (A12); also elsewhere on the board
TAP_VAB13: U10.48 (VAB13), U13.26 (A13); also elsewhere on the board
TAP_VDA0: U10.37 (VDA0), U11.60 (VDA0), U12.11 (D0); also elsewhere on the board
TAP_VDA1: U10.38 (VDA1), U11.61 (VDA1), U12.12 (D1); also elsewhere on the board
TAP_VDA2: U10.39 (VDA2), U11.62 (VDA2), U12.13 (D2); also elsewhere on the board
TAP_VDA3: U10.40 (VDA3), U11.63 (VDA3), U12.15 (D3); also elsewhere on the board
TAP_VDA4: U10.41 (VDA4), U11.64 (VDA4), U12.16 (D4); also elsewhere on the board
TAP_VDA5: U10.42 (VDA5), U11.65 (VDA5), U12.17 (D5); also elsewhere on the board
TAP_VDA6: U10.43 (VDA6), U11.66 (VDA6), U12.18 (D6); also elsewhere on the board
TAP_VDA7: U10.44 (VDA7), U11.67 (VDA7), U12.19 (D7); also elsewhere on the board
TAP_VDB0: U10.28 (VDB0), U11.51 (VDB0), U11.69 (EXT0), U13.11 (D0); also elsewhere on the board
TAP_VDB1: U10.29 (VDB1), U11.52 (VDB1), U11.70 (EXT1), U13.12 (D1); also elsewhere on the board
TAP_VDB2: U10.30 (VDB2), U11.53 (VDB2), U11.71 (EXT2), U13.13 (D2); also elsewhere on the board
TAP_VDB3: U10.31 (VDB3), U11.54 (VDB3), U11.72 (EXT3), U13.15 (D3); also elsewhere on the board
TAP_VDB4: U10.32 (VDB4), U11.55 (VDB4), U11.73 (EXT4), U13.16 (D4); also elsewhere on the board
TAP_VDB5: U10.33 (VDB5), U11.56 (VDB5), U11.74 (EXT5), U13.17 (D5); also elsewhere on the board
TAP_VDB6: U10.34 (VDB6), U11.57 (VDB6), U11.75 (EXT6), U13.18 (D6); also elsewhere on the board
TAP_VDB7: U10.35 (VDB7), U11.58 (VDB7), U11.76 (EXT7), U13.19 (D7); also elsewhere on the board
TAP_XIN: U10.100 (XIN), U11.31 (XIN); also elsewhere on the board
TAP_~5M~: U10.93 (~5MOUT), U10.97 (~5MIN), U11.38 (~5MIN); also elsewhere on the board
TAP_~BURST~: U11.1 (~BURST); also elsewhere on the board
TAP_~CSYNC~: U11.100 (~CSYNC); also elsewhere on the board
TAP_~HCLD~: U10.92 (~HCLD), U11.39 (~HCLD); also elsewhere on the board
TAP_~OVER~: U10.94 (~OVER), U11.37 (~OVER1), U11.50 (~OVER2); also elsewhere on the board
TAP_~PARD~: U10.3 (~PARD), U11.7 (~PARD); also elsewhere on the board
TAP_~PAWR~: U10.4 (~PAWR), U11.6 (~PAWR); also elsewhere on the board
TAP_~VAWR~: U10.78 (~VAWR), U12.27 (~WE); also elsewhere on the board
TAP_~VBWR~: U10.79 (~VBWR), U13.27 (~WE); also elsewhere on the board
TAP_~VCLD~: U10.91 (~VCLD), U11.40 (~VCLD); also elsewhere on the board
TAP_~VRD~: U10.80 (~VRD), U12.22 (~OE), U13.22 (~OE); also elsewhere on the board

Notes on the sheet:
(Not real sure what this RC sink is for.)
(Not sure why VBD* is hooked up to EXT*.)
Configurable pullup/pulldown for testing hi-z data bus
5V bulk decoupling
